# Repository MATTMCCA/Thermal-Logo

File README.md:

# Thermal Logo Business Card
A business card that "prints" the company logo on thermal paper.

Works with Arduino IDE to allow for easy experimentation. The HW design is based on Adafruit's *itsy bitsy* so I could benefit from there bootloader.

## Now on Rev_2

These Business Cards are not for sale/resale. They are strictly for networking, and **Thermal Printer Shenanigans**. Please do-not misuse the design or business cards, any injury that occurs as a result of malintent or negligence, I am not responsible for. 

#### This device will get hot enough to activate thermal paper, please, *business responsibly*. 

### Borrowed works maintain original license.

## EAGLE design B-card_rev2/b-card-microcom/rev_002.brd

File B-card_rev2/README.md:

# Thermal Logo Business Card
A business card that "prints" the company logo on thermal paper.

# Possible Issues with the Design
- Load resistors might need to be smaller to increase current draw. [piggyback 11's on the vreg channels to get 1.88A, or x2 2.27A, x3 2.72A (*for testing*)]
- IDK if the bootloader I plan on using is compatible with the MCU I nabbed from digikey, I think it will but there is a chance it wont.
- The high current part of the PCB might get a wee bit warm.
- IDK about the switch I picked.
- Still no power switch
- No safety measures in place.
- Publishing my contact details online... not too bright... but oh well.
- My confidence level is 65% (kinda high, its usually only 40%) [Lower Now... 40%, I got cocky]
- **OH WOW!, I should have inverted the QR code.....** [fixed on PCB] 
- **OH WOW!, the usb is wired wrong, so... that stinks...** (I'll just nix the resistors and rewire to test) [fixed on PCB]

### Boards have been sent to fab, two assemblies worth of parts have been ordered.

Parts Came [12/29/2021], just wating on boards.

### Amazon Stuff

[Battery A](https://www.amazon.com/dp/B07DNCK7V2)

[Battery B](https://www.amazon.com/dp/B06ZY6J1P8)

[JST-SM 2-pin](https://www.amazon.com/dp/B01EJI8TQK)

[Fiberglass Tape](https://www.amazon.com/dp/B00823I7B6)

[36 gauge **NiCr** Wire](https://www.amazon.com/dp/B07CHTXZYW)

### Other

[0.4mmm Vias](https://www.voltera.io/store/consumables/rivets-0-4mm)

[Via Set Tool](https://www.voltera.io/store/consumables/rivet-tool)

#### Notes:
You cant really solder **NiCr**, its nickle and chrome, that chemistry would respond better to 'welding'. Since I don't have a tiny spot welder... yet.... I opted for permanent mechanical fasteners. Is this perfect? NO, dose it work? YES!

[Hmmm...](https://www.amazon.com/dp/B093SMWQ2Q) Amazon sells spot welders, might have to get one...

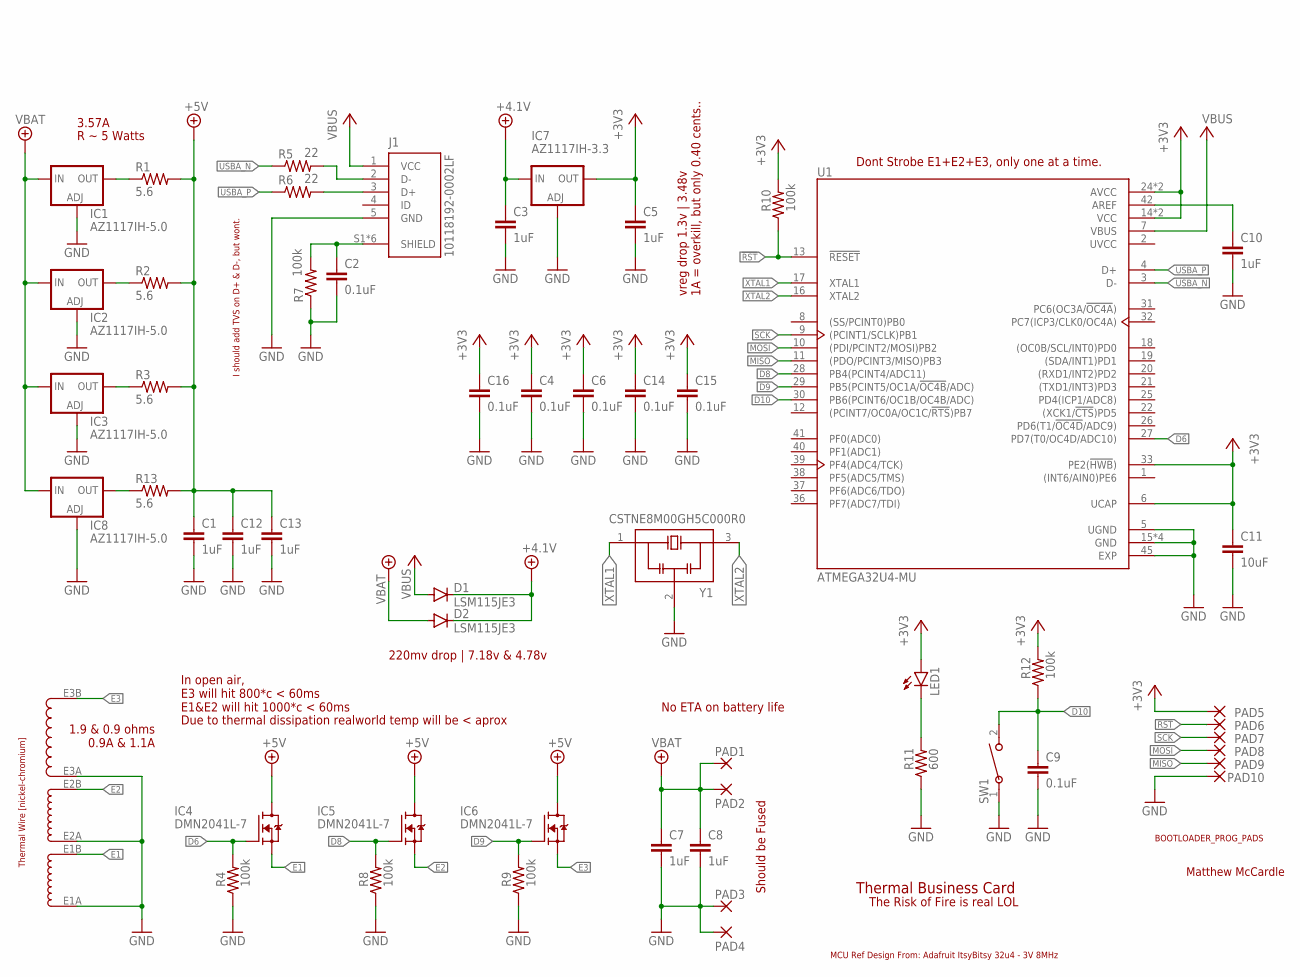
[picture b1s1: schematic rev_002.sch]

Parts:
C1, C3, C5, C7, C8, C10, C12, C13: 1uF; C0603
C2, C4, C6, C9, C14, C15, C16: 0.1uF; C0603
C11: 10uF; C0603
D1, D2: LSM115JE3; DO214BA
IC1, IC2, IC3, IC8: AZ1117IH-5.0; SOT223
IC4, IC5, IC6: DMN2041L-7; SOT23
IC7: AZ1117IH-3.3; SOT223
J1: 10118192-0002LF; AMPHENOL_10118192-0002LF
LED1: LEDSML0603; SML0603
NICR1: HOT_WIRE; LAYOUT_A
PAD1, PAD4: WIREPADSMD5-2,5; 5-2,5
PAD2, PAD3: WIREPAD2,54/0,9; 2,54/0,9
PAD5, PAD6, PAD7, PAD8, PAD9, PAD10: WIREPADSMD1,27-254; SMD1,27-2,54
R1, R2, R3, R13: 5.6; R2512
R4, R7, R8, R9, R10, R12: 100k; R0603
R5, R6: 22; R0603
R11: 600; R0603
SW1: B3AL-1000P; SW_B3AL_OMR
U1: ATMEGA32U4-MU; QFN50P700X700X100-45N
Y1: CSTNE8M00GH5C000R0; OSC_CSTNE8M00GH5C000R0

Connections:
!RST: PAD6.1, R10.1, U1.13 (!RESET!)
+3V3: C4.1, C5.1, C6.1, C11.1, C14.1, C15.1, C16.1, IC7.2 (OUT), IC7.4 (OUT), LED1.A, PAD5.1, R10.2, R12.2, U1.6 (UCAP), U1.14 (VCC), U1.24 (AVCC), U1.33 (PE2(!HWB!)), U1.34 (VCC), U1.44 (AVCC)
+4.1V: C3.1, D1.C, D2.C, IC7.3 (IN)
+5V: C1.1, C12.1, C13.1, IC4.D, IC5.D, IC6.D, R1.2, R2.2, R3.2, R13.2
+8V: C7.1, C8.1, D2.A, IC1.3 (IN), IC2.3 (IN), IC3.3 (IN), IC8.3 (IN), PAD1.1, PAD2.1
D6: IC4.G, R4.2, U1.27 (PD7(T0/OC4D/ADC10))
D8: IC5.G, R8.2, U1.28 (PB4(PCINT4/ADC11))
D9: IC6.G, R9.2, U1.29 (PB5(PCINT5/OC1A/!OC4B!/ADC))
D10: C9.1, R12.1, SW1.2, U1.30 (PB6(PCINT6/OC1B/OC4B/ADC))
E1: IC4.S, NICR1.E1B
E2: IC5.S, NICR1.E2B
E3: IC6.S, NICR1.E3B
GND: C1.2, C2.2, C3.2, C4.2, C5.2, C6.2, C7.2, C8.2, C9.2, C10.2, C11.2, C12.2, C13.2, C14.2, C15.2, C16.2, IC1.1 (ADJ), IC2.1 (ADJ), IC3.1 (ADJ), IC7.1 (ADJ), IC8.1 (ADJ), J1.5 (GND), NICR1.E1A, NICR1.E2A, NICR1.E3A, PAD3.1, PAD4.1, PAD10.1, R4.1, R7.1, R8.1, R9.1, R11.1, SW1.1, U1.5 (UGND), U1.15 (GND), U1.23 (GND), U1.35 (GND), U1.43 (GND), U1.45 (EXP), Y1.2 (GND)
MISO: PAD9.1, U1.11 ((PDO/PCINT3/MISO)PB3)
MOSI: PAD8.1, U1.10 ((PDI/PCINT2/MOSI)PB2)
unnamed: IC8.2 (OUT), IC8.4 (OUT), R13.1
unnamed: C10.1, U1.42 (AREF)
unnamed: C2.1, J1.S1 (SHIELD), J1.S2 (SHIELD), J1.S3 (SHIELD), J1.S4 (SHIELD), J1.S5 (SHIELD), J1.S6 (SHIELD), R7.2
unnamed: LED1.C, R11.2
unnamed: IC3.2 (OUT), IC3.4 (OUT), R3.1
unnamed: IC2.2 (OUT), IC2.4 (OUT), R2.1
unnamed: IC1.2 (OUT), IC1.4 (OUT), R1.1
SCK: PAD7.1, U1.9 ((PCINT1/SCLK)PB1)
USBA_N: R5.1, U1.3 (D-)
USBA_P: R6.1, U1.4 (D+)
USBB_N: J1.2 (D-), R5.2
USBB_P: J1.3 (D+), R6.2
UVCC: U1.2 (UVCC)
VBUS: D1.A, J1.1 (VCC), U1.7 (VBUS)
XTAL1: U1.17 (XTAL1), Y1.1 (IN)
XTAL2: U1.16 (XTAL2), Y1.3 (OUT)

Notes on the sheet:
MCU Ref Design From: Adafruit ItsyBitsy 32u4 - 3V 8MHz
I should add TVS on D+ & D-, but wont.
BOOTLOADER_PROG_PADS
Matthew McCardle
Thermal Wire [nickel-chromium]
Thermal Business Card
3.57A
R ~ 5 Watts
220mv drop | 7.18v & 4.78v
vreg drop 1.3v | 3.48v 1A = overkill, but only 0.40 cents..
1.9 & 0.9 ohms 0.9A & 1.1A
Should be Fused
In open air, E3 will hit 800*c < 60ms E1&E2 will hit 1000*c < 60ms
Due to thermal dissipation realworld temp will be < aprox
The Risk of Fire is real LOL
Dont Strobe E1+E2+E3, only one at a time.
No ETA on battery life

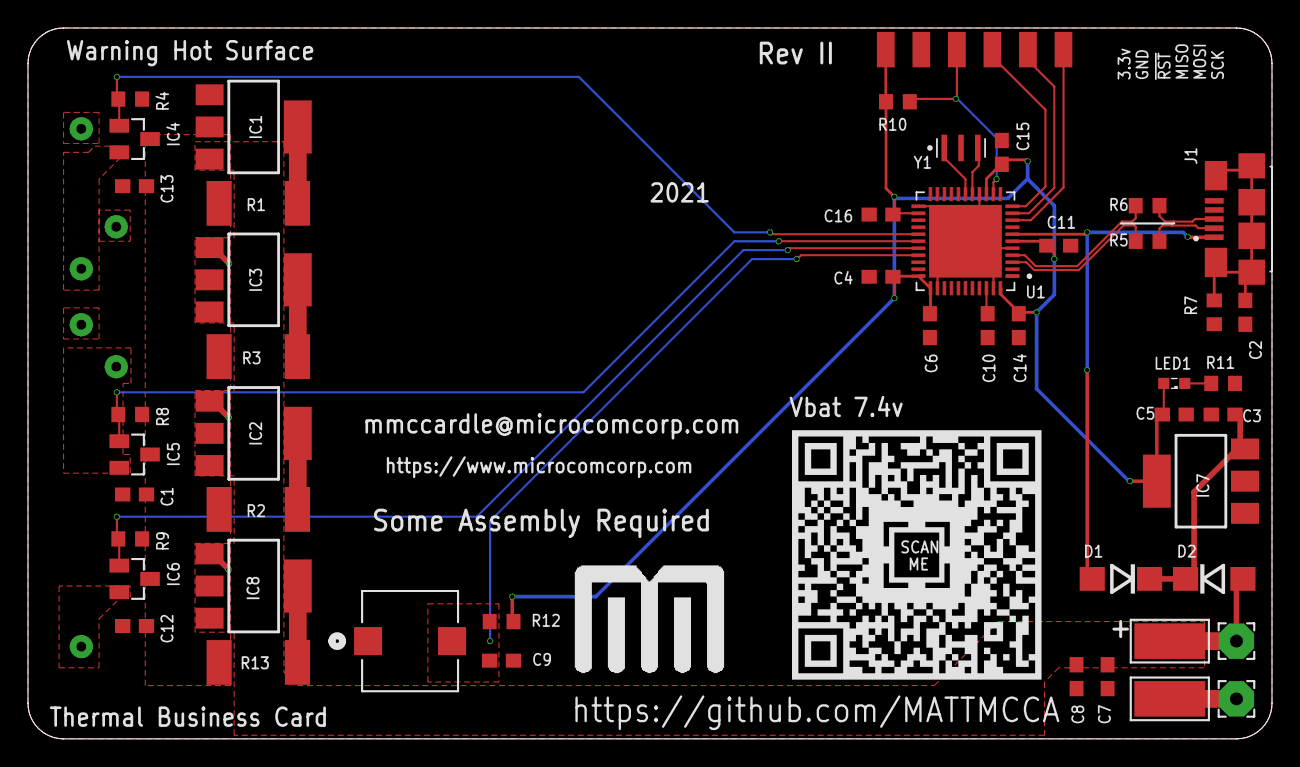
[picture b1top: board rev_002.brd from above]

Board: 2 copper layers, 88.9 x 50.8 mm, 57 parts (0 on the bottom side), 30 nets.

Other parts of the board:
U$1: LINK_INV
U$2: MCOM

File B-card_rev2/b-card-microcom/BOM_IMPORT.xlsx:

Qty | Value | Device | Package | Parts | Description | DIGI-KEY_PART_NUMBER
8 | 1uF | C-EUC0603 | C0603 | C1, C3, C5, C7, C8, C10, C12, C13 | CAPACITOR, European symbol | 399-3118-1-ND
6 | 100k | R-US_R0603 | R0603 | R4, R7, R8, R9, R10, R12 | RESISTOR, American symbol | RMCF0603FT100KCT-ND
6 | WIREPADSMD1,27-254 | WIREPADSMD1,27-254 | SMD1,27-2,54 | PAD5, PAD6, PAD7, PAD8, PAD9, PAD10 | Wire PAD connect wire on PCB | NOT A REAL PART
4 | 5.6 | R-US_R2512 | R2512 | R1, R2, R3, R13 | RESISTOR, American symbol | CPA25Q5.6CT-ND
4 | AZ1117IH-5.0 | LD117ASTR | SOT223 | IC1, IC2, IC3, IC8 | Low drop fixed and adjustable positive voltage regulators 1 A | AZ1117IH-5.0TRG1DICT-ND
3 | DMN2041L-7 | DS31126 | SOT23 | IC4, IC5, IC6 |  | DMN2041L-7DICT-ND
7 | 0.1uF | C-EUC0603 | C0603 | C2, C9, C14, C15, C16, C6, C4 | CAPACITOR, European symbol | 1276-1006-1-ND
2 | 22 | R-US_R0603 | R0603 | R5, R6 | RESISTOR, American symbol | RMCF0603FT22R0CT-ND
2 | LSM115JE3 | DIODE-DO214BA | DO214BA | D1, D2 | DIODE | LSM115JE3/TR13CT-ND
2 | WIREPAD2,54/0,9 | WIREPAD2,54/0,9 | 2,54/0,9 | PAD2, PAD3 | Wire PAD connect wire on PCB | NOT A REAL PART
2 | WIREPADSMD5-2,5 | WIREPADSMD5-2,5 | 5-2,5 | PAD1, PAD4 | Wire PAD connect wire on PCB | NOT A REAL PART
1 | GREEN | LEDSML0603 | SML0603 | LED1 | LED | 732-12017-1-ND
1 | 10118192-0002LF | 10118192-0002LF | AMPHENOL_10118192-0002LF | J1 | USB - micro B USB 2.0 Receptacle Connector 5 Position Surface Mount, Right Angle | 609-5379-1-ND
1 | 10uF | C-EUC0603 | C0603 | C11 | CAPACITOR, European symbol | 1276-1038-1-ND
1 | 600 | R-US_R0603 | R0603 | R11 | RESISTOR, American symbol | 738-RMCF0603FG604RCT-ND
1 | ATMEGA32U4-MU | ATMEGA32U4-MU | QFN50P700X700X100-45N | U1 | 8-bit Microcontrollers - MCU AVR USB 32K FLASH INDUSTRIA | ATMEGA32U4-MU-ND
1 | AZ1117IH-3.3 | LD117ASTR | SOT223 | IC7 | Low drop fixed and adjustable positive voltage regulators 1 A | AZ1117IH-3.3TRG1DICT-ND
1 | B3AL-1000P | B3AL-1000P | SW_B3AL_OMR | SW1 |  | SW1216CT-ND
1 | CSTNE8M00GH5C000R0 | CSTNE8M00GH5C000R0 | OSC_CSTNE8M00GH5C000R0 | Y1 | 8MHz Ceramic Resonator Built in Capacitor 33pF ±0.13% 40 Ohms -40°C ~ 125°C Sur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 | 490-17961-1-ND, ALT=50-ECS-CTE-8.00-10-CT-ND
1 | HOT_WIRE | HOT_WIRE | LAYOUT_A | NICR1 |  | NOT A REAL PART

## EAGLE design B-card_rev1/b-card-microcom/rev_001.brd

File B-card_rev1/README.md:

# Thermal Logo Business Card
A business card that "prints" the company logo on thermal paper.

# Possible Issues with the Design
- The `TPS61097A-33` can handle voltages from 0.9 - 5.5, that's fine, but as the voltage on the input sags, the effective output current also sags. Will < 200mA be enough to power the MCU? (I suspect not)
- The super cap used to hold vin high will deplete too quickly based on the projected current consumption of the design. However, since the heaters wont have a contentious draw on the battery, this might actually work.... I hope
- The 'supply' battery I have in mind can do a contentious 1A, I'm really going to be pushing the limits of the battery. The heaters are an effective short, were talking .9 ohms - 1.9 ohms. @ 3.3v, that's almost 2A. I only performed tests at 5v current limited at 2A, 'this' supply may be too weak to handle the load.
- I have a feeling parts of this design will fail due to spec.
- Giving out business cards that heat up and run the risk of failure could be bad.... seconds thoughts about the project...

# Low Voltage Test

Turns out running at 3.3 with the current choked @ 2 Amps dose heat up the nickle chromium wire to the point of activation, it just takes longer due to the lower effective wattage ~100ms. A possible solution may be to preheat the wire, thus reducing the time needed to reach the activation temperature.

Something to note, during the life of the battery, as the battery becomes depleted, the time needed to activate the paper will become greater. I may be-able to measure vbat during runtime and compensate for delta time.

A safety mechanism may be needed, the paper will act as a heat sink. If the elements are active without paper contact they may prematurely fail.

And a power switch may come in handy, but the likelihood of a client actually building the device is un-probable, this is more of a show piece.

# Addendum

After going through half a roll of [cheap thermal stock](https://www.amazon.com/POS1-Thermal-Paper-diameter-CORELESS/dp/B0785M4982) I came to the conclusion that the 'current' design wont work. 

Solution: Use the `AP1509-50SG-13` to regulate an [rc battery](https://www.amazon.com/Blomiky-1500mAh-Battery-Charger-Helicopter/dp/B07DNCK7V2/) down to 5v@2A, this ic dose not state that there is over current protection, but rather **Current-Limit Protection** , so I think this might work. 

This allows me to nix the battery charger on the pcb, I'm still apprehensive about only supplying the mcu with 200ma, it *should* work, but the official numbers say otherwise. Actually, I could just nix the 3.3v regulator since I have an uber cap to keep the system up during brownout. Or use an LDO linear reg. uber down to 3.3v@300ma from 5v.... that might be ok.

# Addendum Part 2
Ok so... I guess the atmega32u4 can run down to 3v with a lethargic clock, so the need for the 3.3 vreg is void. Ill just run the 8Mhz clock at 5v ~4.8v. If the reservoir cap is charged at 5v, I can operate over a 1.7v sag. Plus! I found [this](https://www.digikey.com/en/products/detail/henlv-power/WRD05S05-10W/15780166) gem, Its through hole, but fits my power requirements. The datasheets in Chinese, so I don't know if it has over current protection, or if its limited. 

New game plan, nix the regulators, drop in a dc/dc power module. Now I don't have to worry about the vreg layout being perfect for maximum efficiency. I might be-able to socket the dc module so no leads stick out the bottom. If not, oh well.

### From [Datasheet](http://www.henlv.com.cn/kin/php/upload/20200924/1600919314377087.pdf) (wrong datasheet though)
`Have good shielding anti-interference performance and electromagnetic compatibility, output overcurrent,
Overheating protection, Self-recovery and other functions.`

...so I don't know if it will drop out or limit the current, I suspect it will drop out ("*self recovery*"), that's what most do (this could be problematic).

# Addendum Part 3
I blew out the nickle chromium wire riveted to my test PCB. The good news is, I was not able to measure any voltage sag on the 7.4v 600mAh battery during **spontaneous vaporization** of the wire. After more destructive testing, I do need to regulate the element voltage, and probably limit the current to a sane amount. Those batteries are WAY better than I thought they would be. I may be able to get away with a linear Vreg capped at 2A for the elements, instead of the pricey DC switching modules with possible over current dropout.

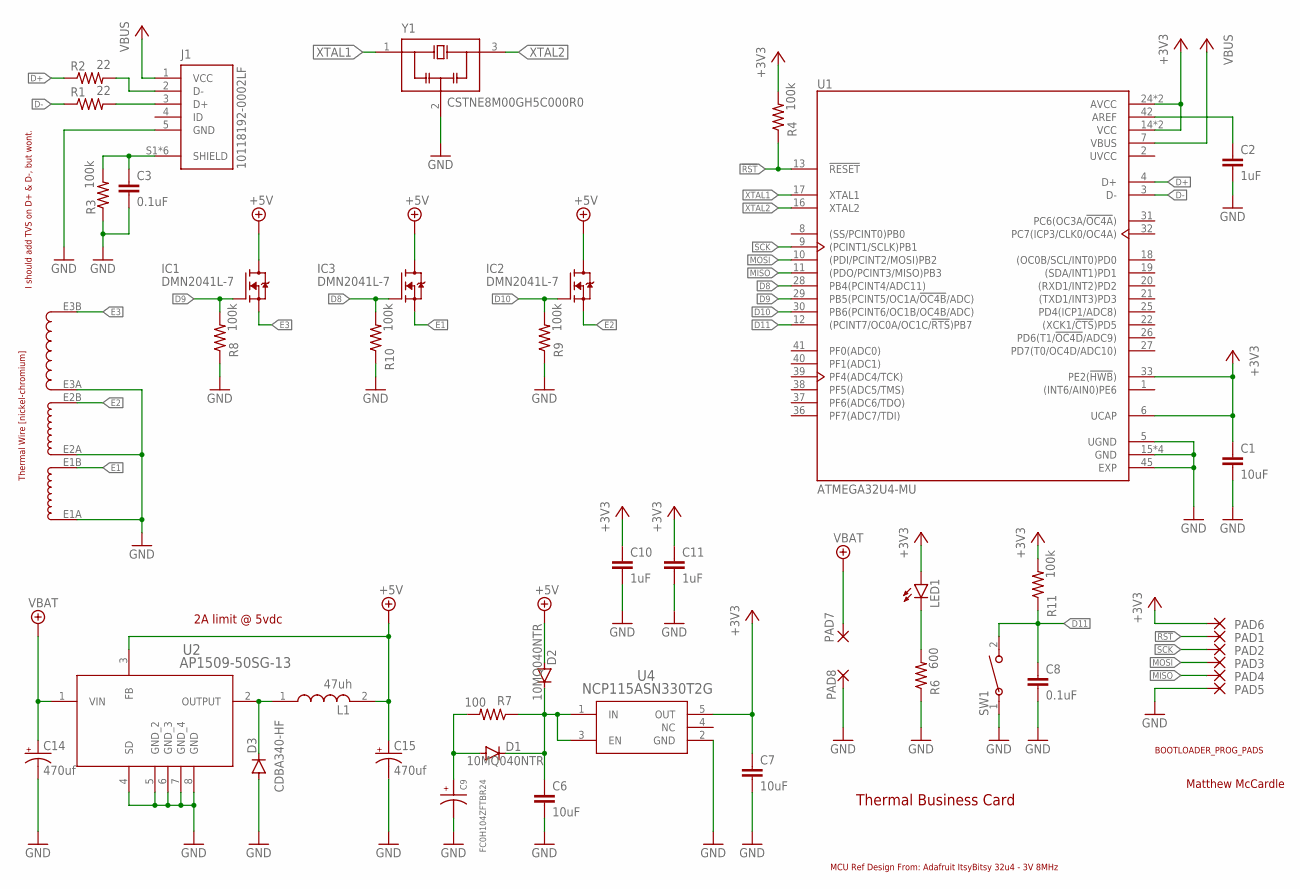
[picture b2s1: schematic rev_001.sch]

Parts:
C1, C6, C7: 10uF; C0603
C2, C10, C11: 1uF; C0603
C3, C8: 0.1uF; C0603
C9: FC0H104ZFTBR24; CAPAE1080X580N
C14, C15: 470uf; UD-4X5,8_NICHICON
D1, D2: 10MQ040NTR; DO-214AC
D3: CDBA340-HF; DO-214AC
IC1, IC2, IC3: DMN2041L-7; SOT23
J1: 10118192-0002LF; AMPHENOL_10118192-0002LF
L1: 47uh; WUERTH_ELEKTRONIK_7447714470_0
LED1: LEDSML0603; SML0603
NICR1: HOT_WIRE; LAYOUT_A
PAD1, PAD2, PAD3, PAD4, PAD5, PAD6: WIREPADSMD1,27-254; SMD1,27-2,54
PAD7, PAD8: WIREPAD2,54/0,9; 2,54/0,9
R1, R2: 22; R0603
R3, R4, R8, R9, R10, R11: 100k; R0603
R6: 600; R0603
R7: 100; R0603
SW1: B3AL-1000P; SW_B3AL_OMR
U1: ATMEGA32U4-MU; QFN50P700X700X100-45N
U2: AP1509-50SG-13; SOP-8L_DIO
U4: NCP115ASN330T2G; TSOP-5-483-N_ONS
Y1: CSTNE8M00GH5C000R0; OSC_CSTNE8M00GH5C000R0

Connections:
!RST: PAD1.1, R4.1, U1.13 (!RESET!)
+3V3: C1.1, C7.1, C10.1, C11.1, LED1.A, PAD6.1, R4.2, R11.2, U1.6 (UCAP), U1.14 (VCC), U1.24 (AVCC), U1.33 (PE2(!HWB!)), U1.34 (VCC), U1.44 (AVCC), U4.5 (OUT)
+5V: C15.+, D2.A, IC1.D, IC2.D, IC3.D, J1.1 (VCC), L1.2, U1.7 (VBUS), U2.3 (FB)
+8V: C14.+, PAD7.1, U2.1 (VIN)
D8: IC3.G, R10.2, U1.28 (PB4(PCINT4/ADC11))
D9: IC1.G, R8.2, U1.29 (PB5(PCINT5/OC1A/!OC4B!/ADC))
D10: IC2.G, R9.2, U1.30 (PB6(PCINT6/OC1B/OC4B/ADC))
D11: C8.1, R11.1, SW1.2, U1.12 ((PCINT7/OC0A/OC1C/!RTS!)PB7)
D+: R2.1, U1.4 (D+)
D-: R1.1, U1.3 (D-)
E1: IC3.S, NICR1.E1B
E2: IC2.S, NICR1.E2B
E3: IC1.S, NICR1.E3B
GND: C1.2, C2.2, C3.2, C6.2, C7.2, C8.2, C9.2, C10.2, C11.2, C14.-, C15.-, D3.A, J1.5 (GND), NICR1.E1A, NICR1.E2A, NICR1.E3A, PAD5.1, PAD8.1, R3.1, R6.1, R8.1, R9.1, R10.1, SW1.1, U1.5 (UGND), U1.15 (GND), U1.23 (GND), U1.35 (GND), U1.43 (GND), U1.45 (EXP), U2.4 (SD), U2.5 (GND_2), U2.6 (GND_3), U2.7 (GND_4), U2.8 (GND), U4.2 (GND), Y1.2 (GND)
MISO: PAD4.1, U1.11 ((PDO/PCINT3/MISO)PB3)
MOSI: PAD3.1, U1.10 ((PDI/PCINT2/MOSI)PB2)
unnamed: J1.3 (D+), R1.2
unnamed: C2.1, U1.42 (AREF)
unnamed: J1.2 (D-), R2.2
unnamed: C3.1, J1.S1 (SHIELD), J1.S2 (SHIELD), J1.S3 (SHIELD), J1.S4 (SHIELD), J1.S5 (SHIELD), J1.S6 (SHIELD), R3.2
unnamed: LED1.C, R6.2
unnamed: D3.C, L1.1, U2.2 (OUTPUT)
unnamed: C9.1, D1.A, R7.2
unnamed: C6.1, D1.C, D2.C, R7.1, U4.1 (IN), U4.3 (EN)
SCK: PAD2.1, U1.9 ((PCINT1/SCLK)PB1)
UVCC: U1.2 (UVCC)
XTAL1: U1.17 (XTAL1), Y1.1 (IN)
XTAL2: U1.16 (XTAL2), Y1.3 (OUT)

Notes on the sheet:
MCU Ref Design From: Adafruit ItsyBitsy 32u4 - 3V 8MHz
I should add TVS on D+ & D-, but wont.
BOOTLOADER_PROG_PADS
Matthew McCardle
Thermal Wire [nickel-chromium]
Thermal Business Card
2A limit @ 5vdc

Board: 2 copper layers, 44 parts (0 on the bottom side), 27 nets, no tracks yet.

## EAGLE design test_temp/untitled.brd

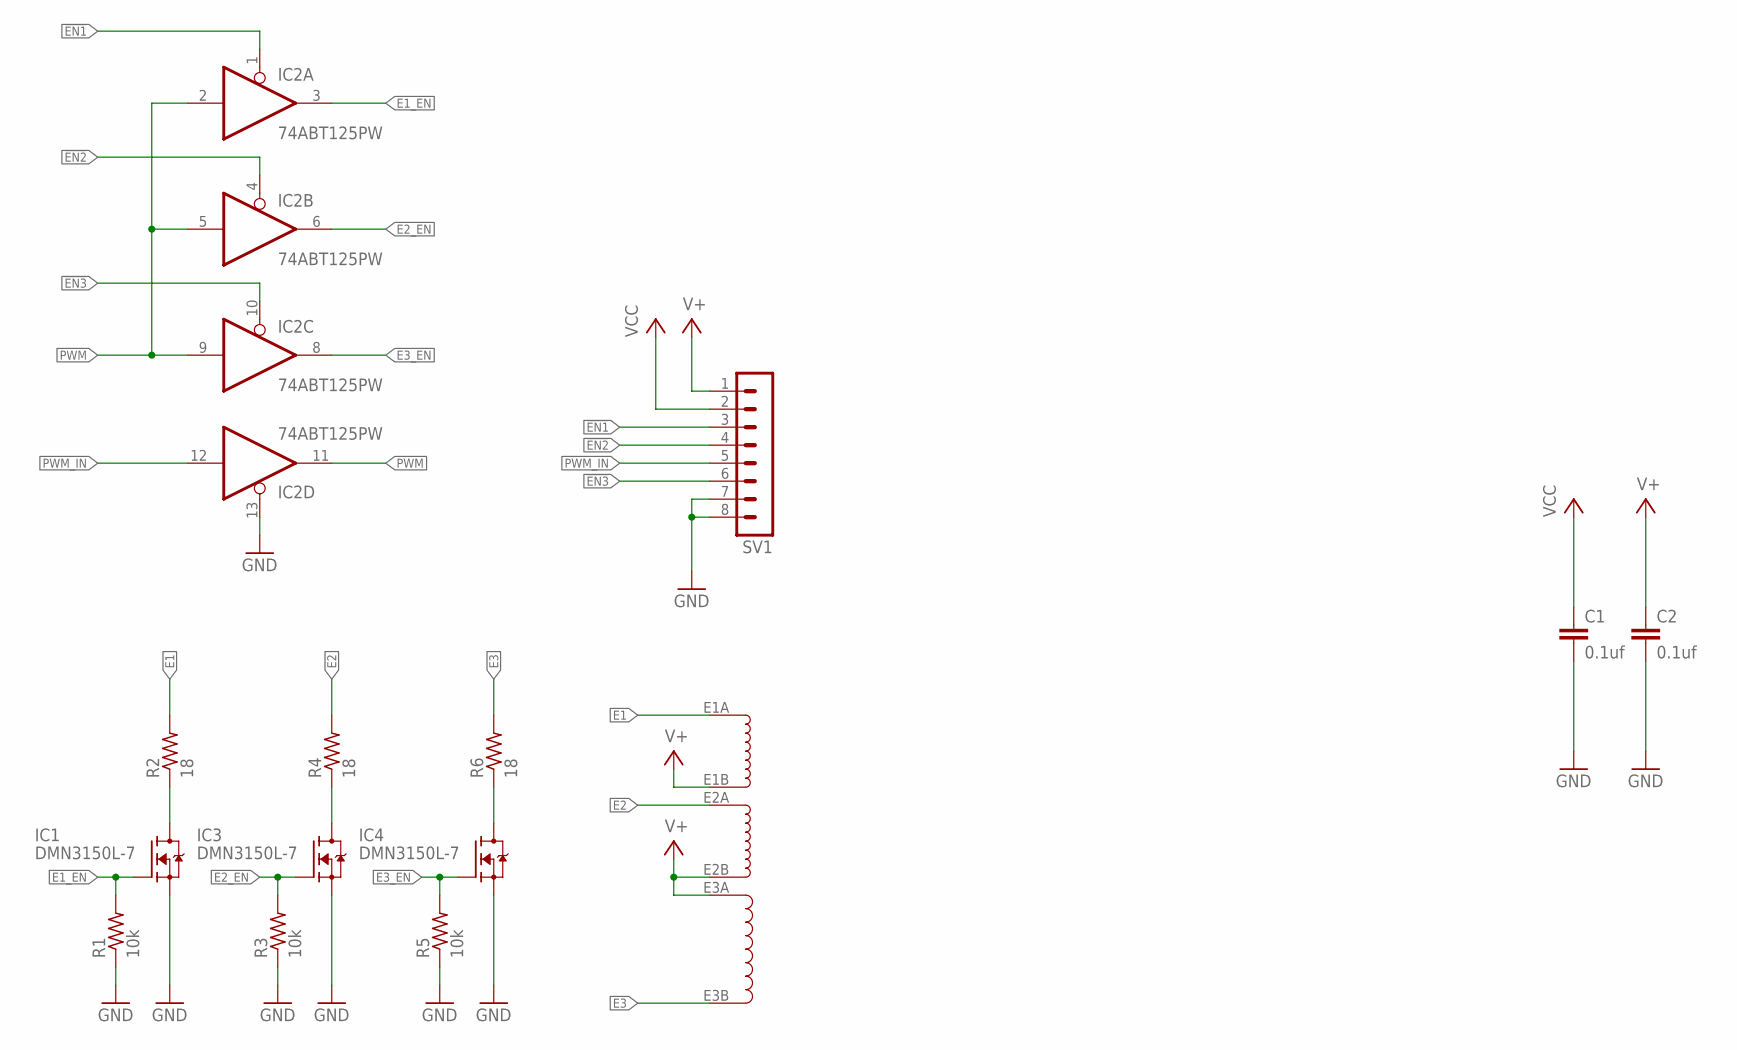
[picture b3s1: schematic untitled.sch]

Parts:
C1, C2: 0.1uf; C0603
IC1, IC3, IC4: DMN3150L-7; SOT23
IC2: 74ABT125PW; TSSOP14
NICR1: HOT_WIRE; LAYOUT_A
R1, R3, R5: 10k; R0603
R2, R4, R6: 18; R2512W
SV1: MA08-1

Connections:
!EN1: IC2.1 (OE), SV1.3
!EN2: IC2.4 (OE), SV1.4
!EN3: IC2.10 (OE), SV1.6
E1: NICR1.E1A, R2.2
E1_EN: IC1.G, IC2.3 (O), R1.2
E2: NICR1.E2A, R4.2
E2_EN: IC2.6 (O), IC3.G, R3.2
E3: NICR1.E3B, R6.2
E3_EN: IC2.8 (O), IC4.G, R5.2
GND: C1.2, C2.2, IC1.S, IC2.7 (GND), IC2.13 (OE), IC3.S, IC4.S, R1.1, R3.1, R5.1, SV1.7, SV1.8
unnamed: IC1.D, R2.1
unnamed: IC3.D, R4.1
unnamed: IC4.D, R6.1
PWM: IC2.2 (I), IC2.5 (I), IC2.9 (I), IC2.11 (O)
PWM_IN: IC2.12 (I), SV1.5
V+: C2.1, NICR1.E1B, NICR1.E2B, NICR1.E3A, SV1.1
VCC: C1.1, IC2.14 (VCC), SV1.2

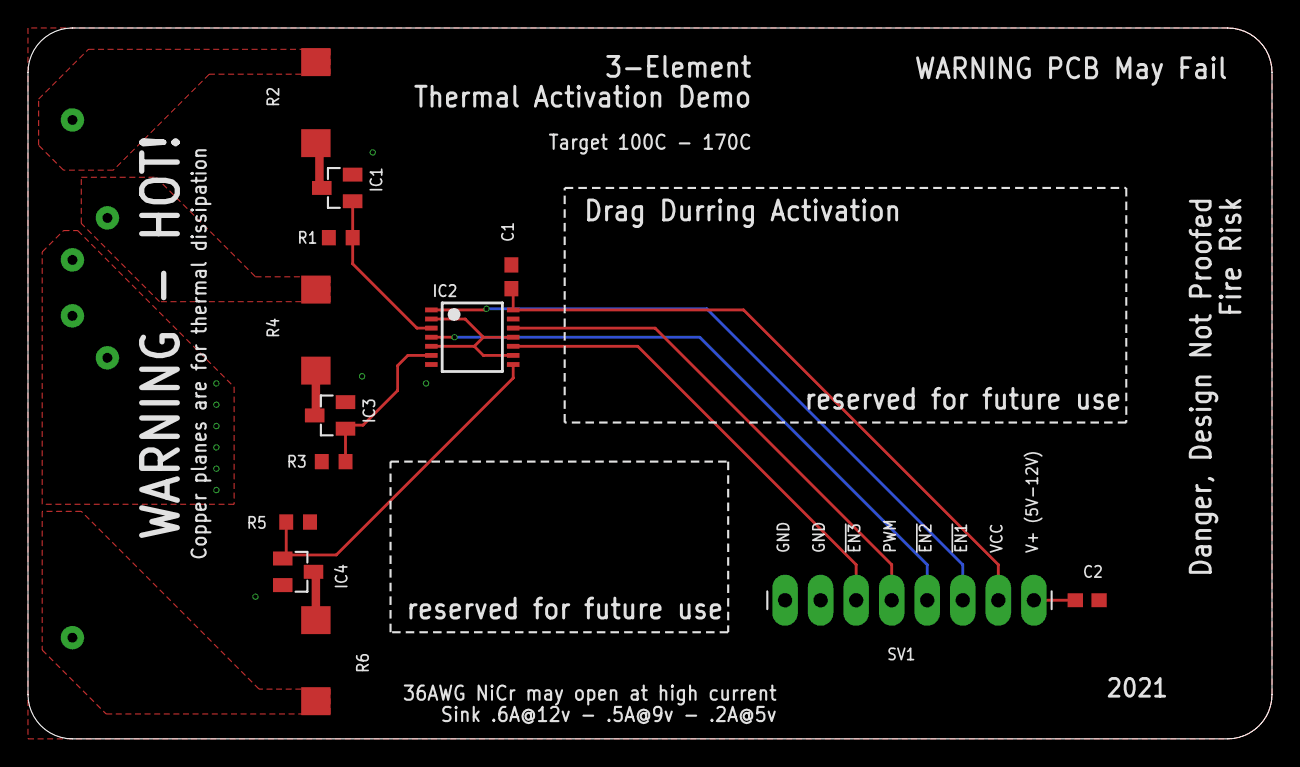
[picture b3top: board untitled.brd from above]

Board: 2 copper layers, 88.9 x 50.8 mm, 14 parts (0 on the bottom side), 17 nets.

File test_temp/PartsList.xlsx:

REF | Val | Part Number | Quantity | Supplier | URL
R1 | 10k | RMCF0603JT10K0CT-ND | 1 | Digikey | https://www.digikey.com/en/products/detail/stackpole-electro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
R2 | 18 | A121160CT-ND | 1 | Digikey | https://www.digikey.com/en/products/detail/te-connectivity-p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
R3 | 10k | RMCF0603JT10K0CT-ND | 1 | Digikey | https://www.digikey.com/en/products/detail/stackpole-electro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
R4 | 18 | A121160CT-ND | 1 | Digikey | https://www.digikey.com/en/products/detail/te-connectivity-p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
R5 | 10k | RMCF0603JT10K0CT-ND | 1 | Digikey | https://www.digikey.com/en/products/detail/stackpole-electro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
R6 | 18 | A121160CT-ND | 1 | Digikey | https://www.digikey.com/en/products/detail/te-connectivity-p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
IC1 | DMN3150 | DMN3150LDICT-ND | 1 | Digikey | https://www.digikey.com/en/products/detail/diodes-incorporat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
IC2 | 74HCS125 | 296-SN74HCS125PWRCT-ND | 1 | Digikey | https://www.digikey.com/en/products/detail/texas-instruments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
IC3 | DMN3150 | DMN3150LDICT-ND | 1 | Digikey | https://www.digikey.com/en/products/detail/diodes-incorporat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
IC4 | DMN3150 | DMN3150LDICT-ND | 1 | Digikey | https://www.digikey.com/en/products/detail/diodes-incorporat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
C1 | .1uf | 732-13187-1-ND | 1 | Digikey | https://www.digikey.com/en/products/detail/w%C3%BCrth-elektr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
C2 | .1uf | 732-13187-1-ND | 1 | Digikey | https://www.digikey.com/en/products/detail/w%C3%BCrth-elektr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
SV1 | 8pos header | 1528-2923-ND | 0 | Digikey | https://www.digikey.com/en/products/detail/adafruit-industri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
 | Nichrome 80, 36AWG |  | 1 | amazon | https://www.amazon.com/Nichrome-80-Gauge-Resistance-Wire/dp/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
 | PTFE Glass Cloth Tape |  | 1 | amazon | https://www.amazon.com/TapeCase-134-3-Fiberglass-PTFE-Tape/d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
 | 0.4mm copper rivets, drill .7mm | 1000283 | 1 | voltera.io | https://www.voltera.io/store/consumables/rivets-0-4mm
 | rivet press tool | 1000288 | 1 | voltera.io | https://www.voltera.io/store/consumables/rivet-tool

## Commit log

2021-12-05 this
2021-12-05 sent to fab + parts on order
    if this works ill be surprised. it should... but man, I see alot is issues. *fingers crossed*
2021-12-05 Update eagle.epf
    ??
2021-12-07 fixed sch
2021-12-08 Create via_size.png
    I got a package!
2021-12-12 img of PCB
    PCB's from JLC, populated + wire set with Via's
2021-12-13 actual tests
    The damn thing actually kinda works.... I'm surprised!
2021-12-14 test img + code
    Power supply was limited at 5V@2A during test.
2021-12-18 wip
    work in progress, not very confident in the design at the moment.
    Charging a 2ah batt @ 500ma will take like 4 hours.
    now sure how low the voltage will sag during operation, the risk of brownout is real.
    still need to add a crystal, smd not can.
    JST connector is only rated for 2A, I don't think it will melt, but its out of spec.
    + other issues
2021-12-18 pizza break!
    mmm pizza
2021-12-19 need sleep, 2Bcont
2021-12-26 rev 2
    still not working, builder be warned.
2021-12-26 update
    this should work, Kinda feel like i should be pushing more current though the elements, but its rev 2, we will see.
    Vreg & resistors should stay below the thermal limit. The only thing that should get hot is the activation wire..... mfets should stay cool too i hope.
2021-12-26 renum
2021-12-27 layout kinda done
    I'm not 100% happy with everything yet, but it looks like it could work.
2021-12-27 rev 2 90% done
    I need to give everything a once over before fab, and throw together a parts list.
2021-12-27 revamp
2021-12-27 Update README.md
    wow, cant type today... or any other day... ha
2021-12-28 Inverted QR
    QR looks like poo, I may thin it out.
2021-12-28 Update README.md
    umm, I blame spell check for not know what I was trying to say. Its the computers fault.
2021-12-31 logo logic test
2021-12-31 removed logic
    replaced logic with bitmap & offset value
2022-01-09 not rev-ed
    Changed the sch and board, adapted for higher current.
    Made small change to sketch, removed thermal approx.
    exported new Gerber's.
    changed BOM to reflect new design.
    layout change now ready for fab, still needs a once over to correct any mistakes that I may have missed.
2022-01-09 build pics
    added build pics

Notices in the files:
parts and their libraries:
COPYRIGHT: Copyright (C) 2021 Ultra Librarian. All rights reserved.
